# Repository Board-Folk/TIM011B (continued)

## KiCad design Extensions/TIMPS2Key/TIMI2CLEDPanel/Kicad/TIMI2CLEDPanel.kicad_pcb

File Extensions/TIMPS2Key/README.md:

# TIMPS2Key

ATMega/Arduino based PS/2 Keyboard Adapter. Will soon be adding the daughter board for v1.2 or later main boards which will allow fitting within the original board footprint instead of the related serial circuitry and DIN socket.

## Versions

v0 Prototype / Development board using Arduino Nano and a MAX232.

v1 Final Arduino Nano Version. Now includes sound and i2c output for LED panel.

v2 ATMEGA328 Version of v1

## Notes

For use on v1.2 or later main boards with 5V power output selected, bypass voltage regulator at U3 connecting pins 1 and 3

## TIMI2CLEDPanel

This folder contains an I2C connected board to output the keyboard LED display. It's intended to fit within a 3.5" drive blanking front panel blanking plate.

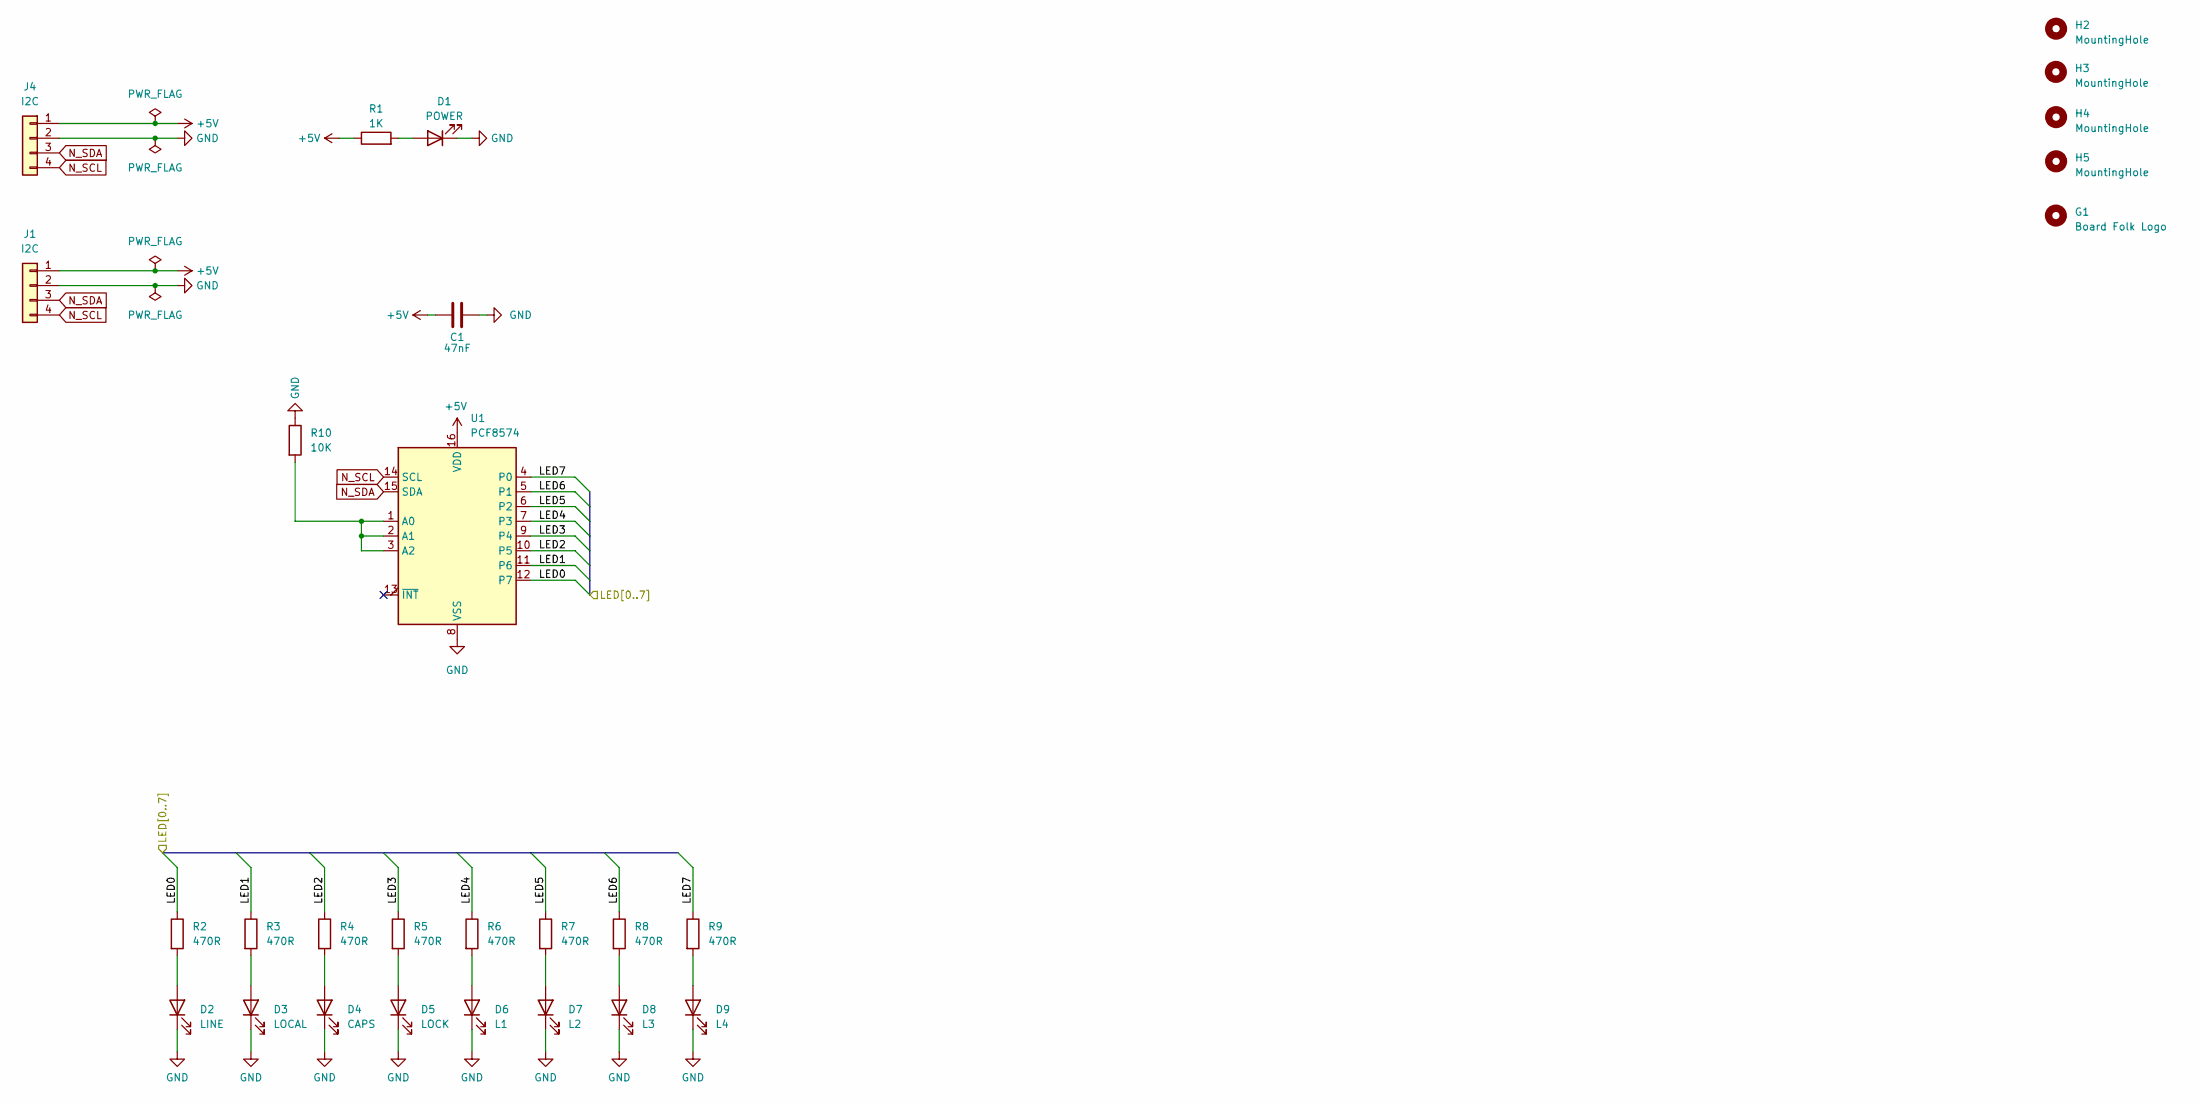
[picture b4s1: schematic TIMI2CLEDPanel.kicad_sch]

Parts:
C1: 47nF; C_Disc_D4.3mm_W1.9mm_P5.00mm
D1: POWER; LED_D3.0mm
D2: LINE; LED_D3.0mm
D3: LOCAL; LED_D3.0mm
D4: CAPS; LED_D3.0mm
D5: LOCK; LED_D3.0mm
D6: L1; LED_D3.0mm
D7: L2; LED_D3.0mm
D8: L3; LED_D3.0mm
D9: L4; LED_D3.0mm
G1: Board Folk Logo; BF8
H2, H3, H4, H5: MountingHole; MountingHole_2.1mm
J1, J4: I2C; PinHeader_1x04_P2.54mm_Vertical
R1: 1K; R_Axial_DIN0204_L3.6mm_D1.6mm_P7.62mm_Horizontal
R2, R3, R4, R5, R6, R7, R8, R9: 470R; R_Axial_DIN0204_L3.6mm_D1.6mm_P7.62mm_Horizontal
R10: 10K; R_Axial_DIN0204_L3.6mm_D1.6mm_P7.62mm_Horizontal
U1: PCF8574; DIP-16_W7.62mm

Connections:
+5V: C1.2, J1.1, J4.1, R1.1, U1.16 (VDD)
/LED0: R2.1, U1.12 (P7)
/LED1: R3.1, U1.11 (P6)
/LED2: R4.1, U1.10 (P5)
/LED3: R5.1, U1.9 (P4)
/LED4: R6.1, U1.7 (P3)
/LED5: R7.1, U1.6 (P2)
/LED6: R8.1, U1.5 (P1)
/LED7: R9.1, U1.4 (P0)
GND: C1.1, D1.1 (K), D2.1 (K), D3.1 (K), D4.1 (K), D5.1 (K), D6.1 (K), D7.1 (K), D8.1 (K), D9.1 (K), J1.2, J4.2, R10.1, U1.8 (VSS)
N_SCL: J1.4, J4.4, U1.14 (SCL)
N_SDA: J1.3, J4.3, U1.15 (SDA)
unnamed: D1.2 (A), R1.2
unnamed: D2.2 (A), R2.2
unnamed: D3.2 (A), R3.2
unnamed: D4.2 (A), R4.2
unnamed: D5.2 (A), R5.2
unnamed: D6.2 (A), R6.2
unnamed: D7.2 (A), R7.2
unnamed: D8.2 (A), R8.2
unnamed: D9.2 (A), R9.2
unnamed: R10.2, U1.1 (A0), U1.2 (A1), U1.3 (A2)

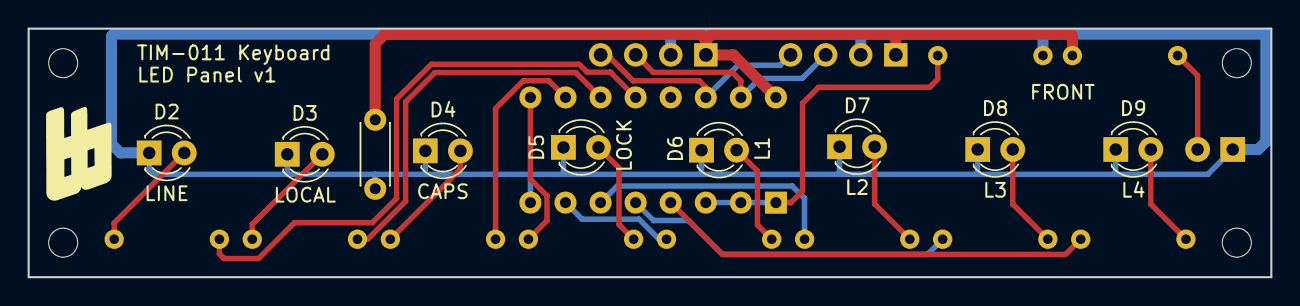
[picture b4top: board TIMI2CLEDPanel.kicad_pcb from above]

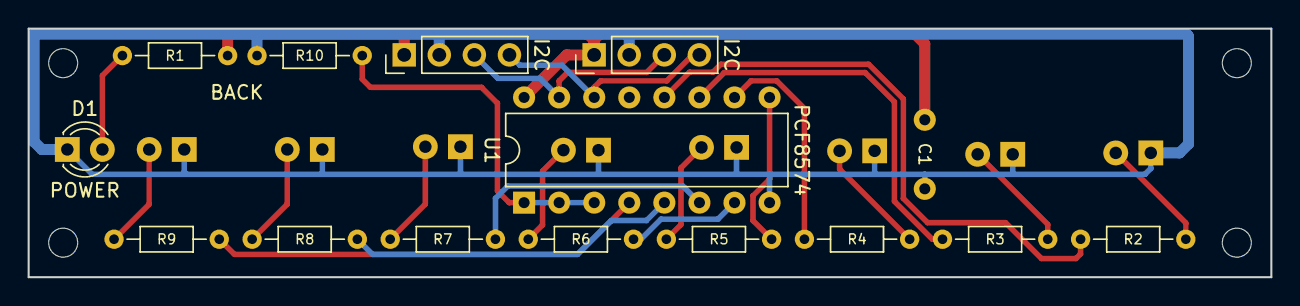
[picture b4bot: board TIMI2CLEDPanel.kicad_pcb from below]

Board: 2 copper layers, 90.0 x 18.0 mm, 28 parts (14 on the bottom side), 22 nets.

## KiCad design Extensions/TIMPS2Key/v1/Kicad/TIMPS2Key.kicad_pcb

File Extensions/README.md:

# TIM-011B Extensions

Extension Boards for the TIM-011B

## TIMPS2Key

ATMega/Arduino based PS/2 Keyboard Adapter.

## TIMAYSound

AY-3-8910/12 expansion board for joystick and sound.

## tim011_video_fix

Video output board to create RGB and composite output from standard TIM-011 video signaling.

## TIMPS2KeyMini

Keyboard daughter card for mainboard v1.2 or later. For fitting a PS/2 keyboard interface within the mainboard footprint.

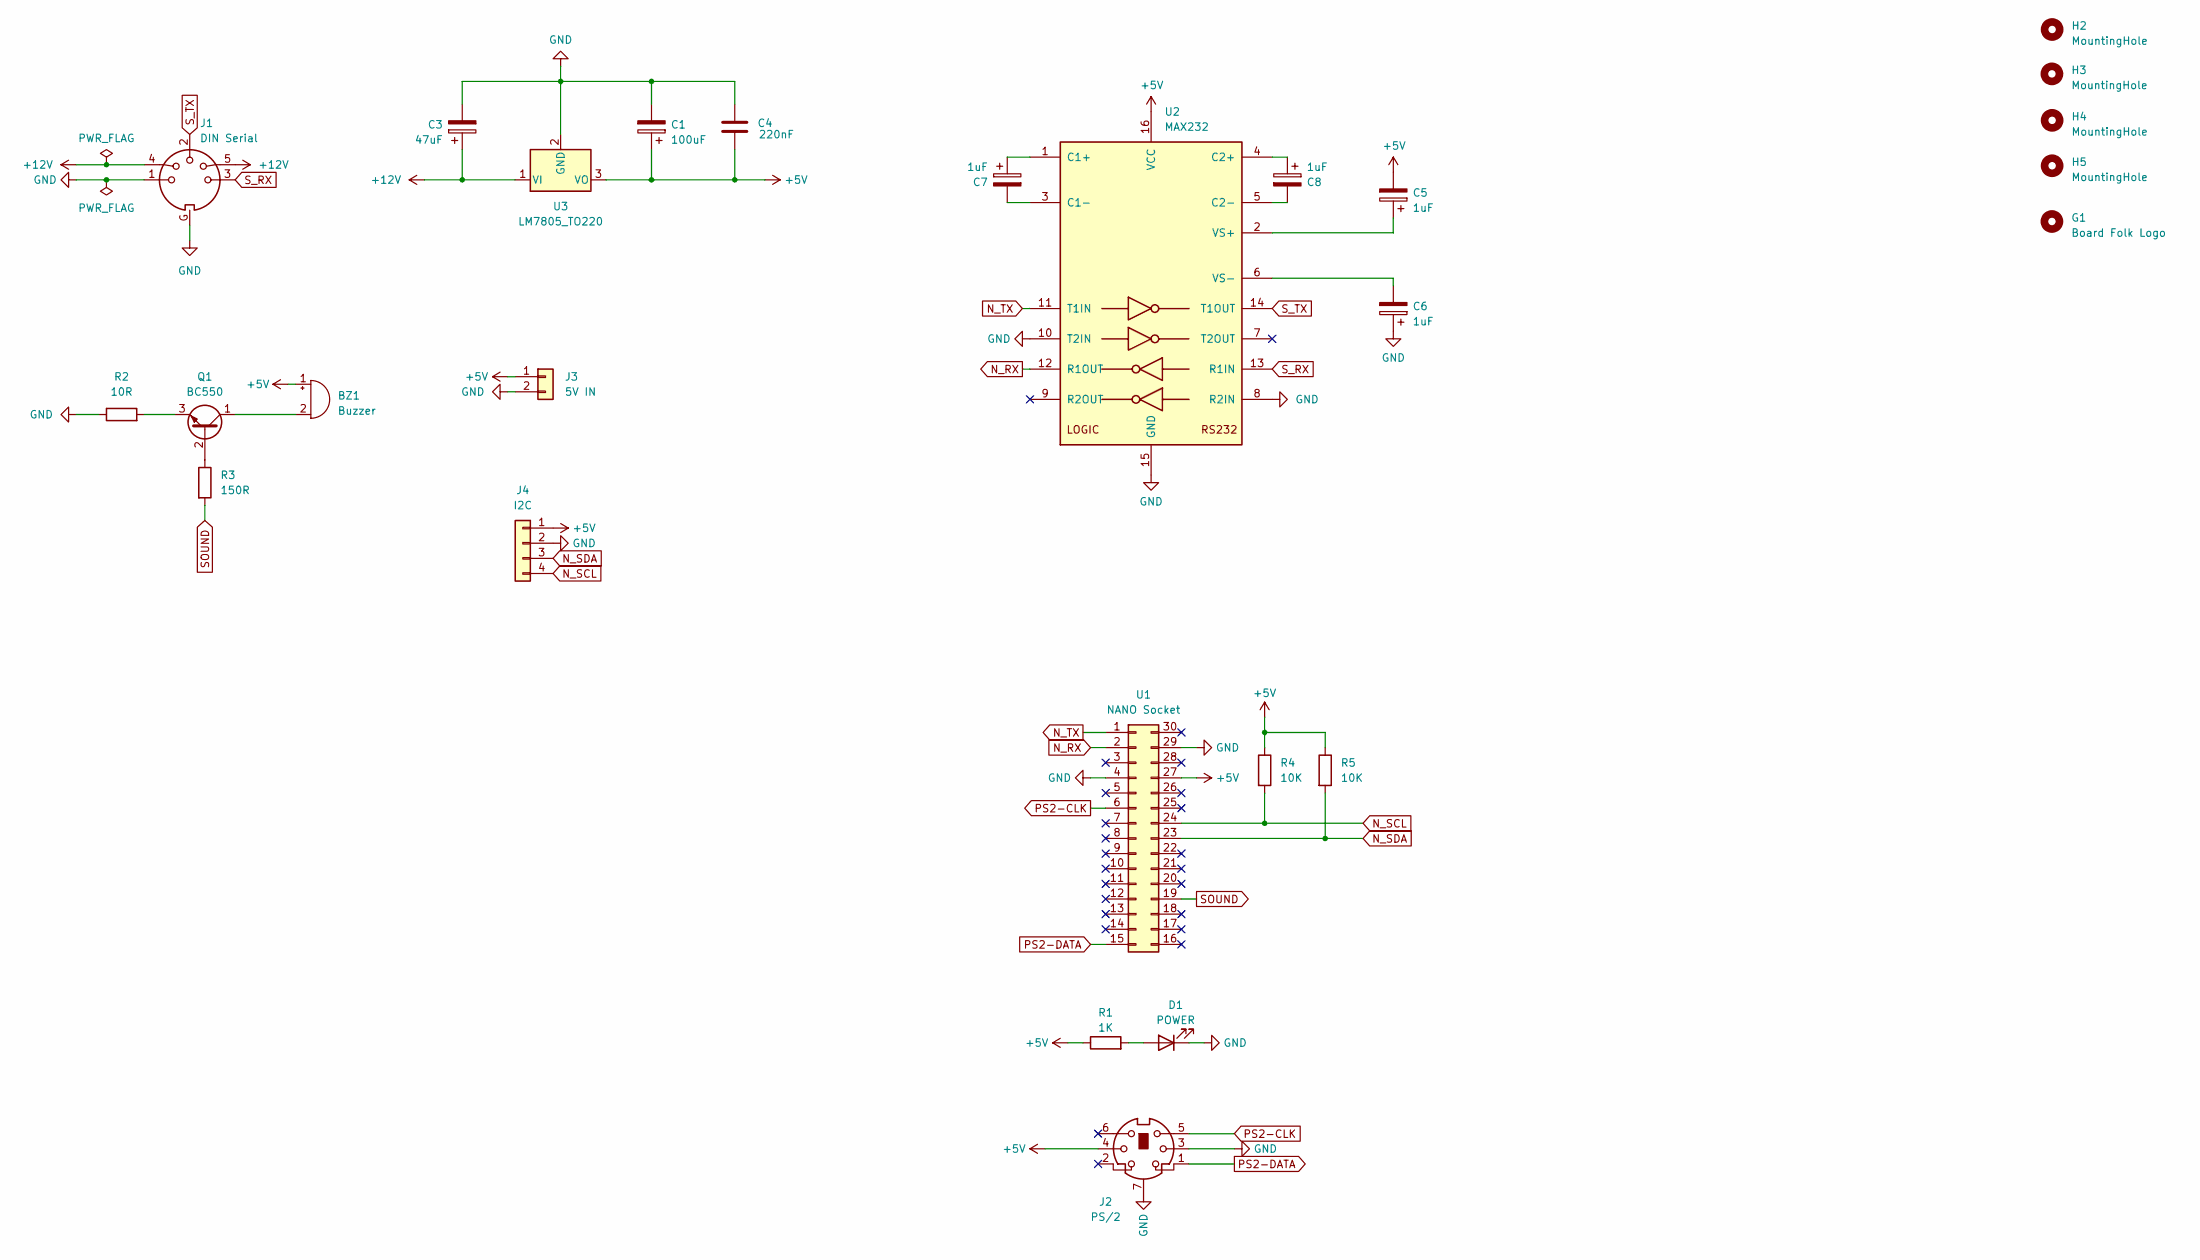
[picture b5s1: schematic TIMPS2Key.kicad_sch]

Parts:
BZ1: Buzzer; MagneticBuzzer_ProSignal_ABT-410-RC
C1: 100uF; CP_Radial_D5.0mm_P2.00mm
C3: 47uF; CP_Radial_D5.0mm_P2.00mm
C4: 220nF; C_Disc_D4.3mm_W1.9mm_P5.00mm
C5, C6, C7, C8: 1uF; CP_Radial_D4.0mm_P2.00mm
D1: POWER; LED_D3.0mm
G1: Board Folk Logo; BF8
H2, H3, H4, H5: MountingHole; MountingHole_2.1mm
J1: DIN Serial; DINSerial
J2: PS/2; Connector_Mini-DIN_Female_6Pin_2rows
J3: 5V IN; PinHeader_1x02_P2.54mm_Vertical
J4: I2C; PinHeader_1x04_P2.54mm_Vertical
Q1: BC550; TO-92_Inline_Wide
R1: 1K; R_Axial_DIN0204_L3.6mm_D1.6mm_P7.62mm_Horizontal
R2: 10R; R_Axial_DIN0204_L3.6mm_D1.6mm_P7.62mm_Horizontal
R3: 150R; R_Axial_DIN0204_L3.6mm_D1.6mm_P7.62mm_Horizontal
R4, R5: 10K; R_Axial_DIN0204_L3.6mm_D1.6mm_P7.62mm_Horizontal
U1: NANO Socket; Arduino_Nano_WithMountingHoles
U2: MAX232; DIP-16_W7.62mm
U3: LM7805_TO220; TO-220-3_Vertical

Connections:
+5V: BZ1.1 (+), C1.1, C4.2, C5.2, J2.4, J3.1, J4.1, R1.1, R4.1, R5.1, U1.27, U2.16 (VCC), U3.3 (VO)
+12V: C3.1, J1.4, J1.5, U3.1 (VI)
GND: C1.2, C3.2, C4.1, C6.1, D1.1 (K), J1.1, J1.G, J2.3, J2.7, J3.2, J4.2, R2.1, U1.4, U1.29, U2.8 (R2IN), U2.10 (T2IN), U2.15 (GND), U3.2 (GND)
N_RX: U1.2, U2.12 (R1OUT)
N_SCL: J4.4, R4.2, U1.24
N_SDA: J4.3, R5.2, U1.23
N_TX: U1.1, U2.11 (T1IN)
unnamed: BZ1.2 (-), Q1.1 (C)
unnamed: D1.2 (A), R1.2
unnamed: Q1.2 (B), R3.1
unnamed: Q1.3 (E), R2.2
unnamed: C7.1, U2.1 (C1+)
unnamed: C7.2, U2.3 (C1-)
unnamed: C8.1, U2.4 (C2+)
unnamed: C8.2, U2.5 (C2-)
unnamed: C5.1, U2.2 (VS+)
unnamed: C6.2, U2.6 (VS-)
PS2-CLK: J2.5, U1.6
PS2-DATA: J2.1, U1.15
SOUND: R3.2, U1.19
S_RX: J1.3, U2.13 (R1IN)
S_TX: J1.2, U2.14 (T1OUT)

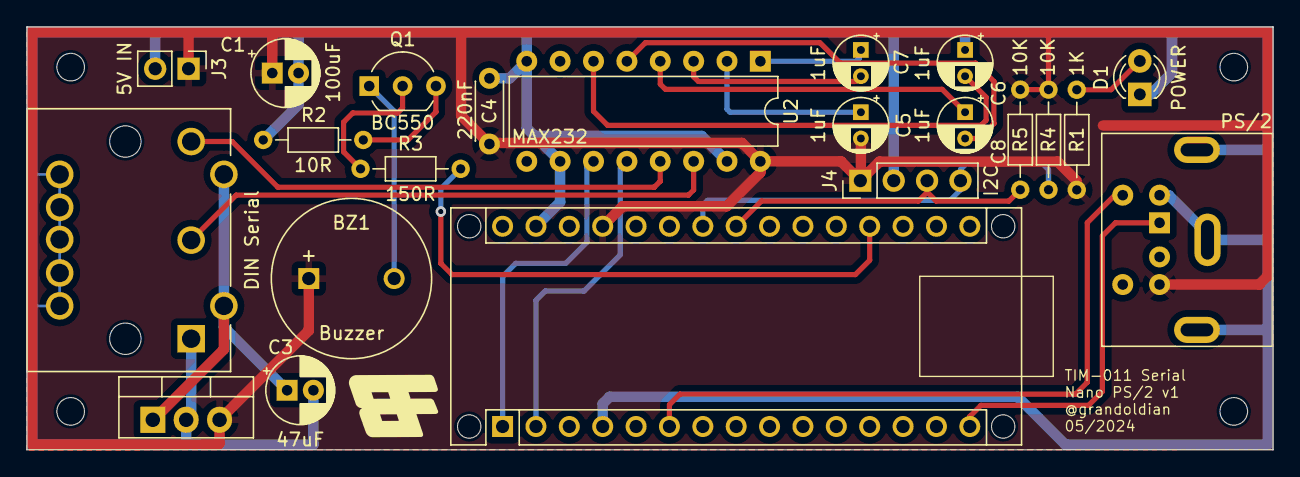
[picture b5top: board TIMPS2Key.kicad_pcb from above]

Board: 2 copper layers, 94.8 x 32.2 mm, 27 parts (0 on the bottom side), 22 nets.

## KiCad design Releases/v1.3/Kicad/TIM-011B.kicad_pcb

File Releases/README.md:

# TIM-011B Releases

Each releases folder contains a Kicad, Gerbers and BOM folder, the latter containing the generated iBOM to help build the board.

Please check out the revision notes, currently on the repository home readme for changes and modifications.

## v1.1

12/04/2024

Initial public release. This doesn't deviate much from the original 1987 board.

## v1.3

16/11/2024

Contains improvements including composite video output, updated oscillators and stability fixes.

## v1.3.1

19/11/2024

Silkscreen fixes only.

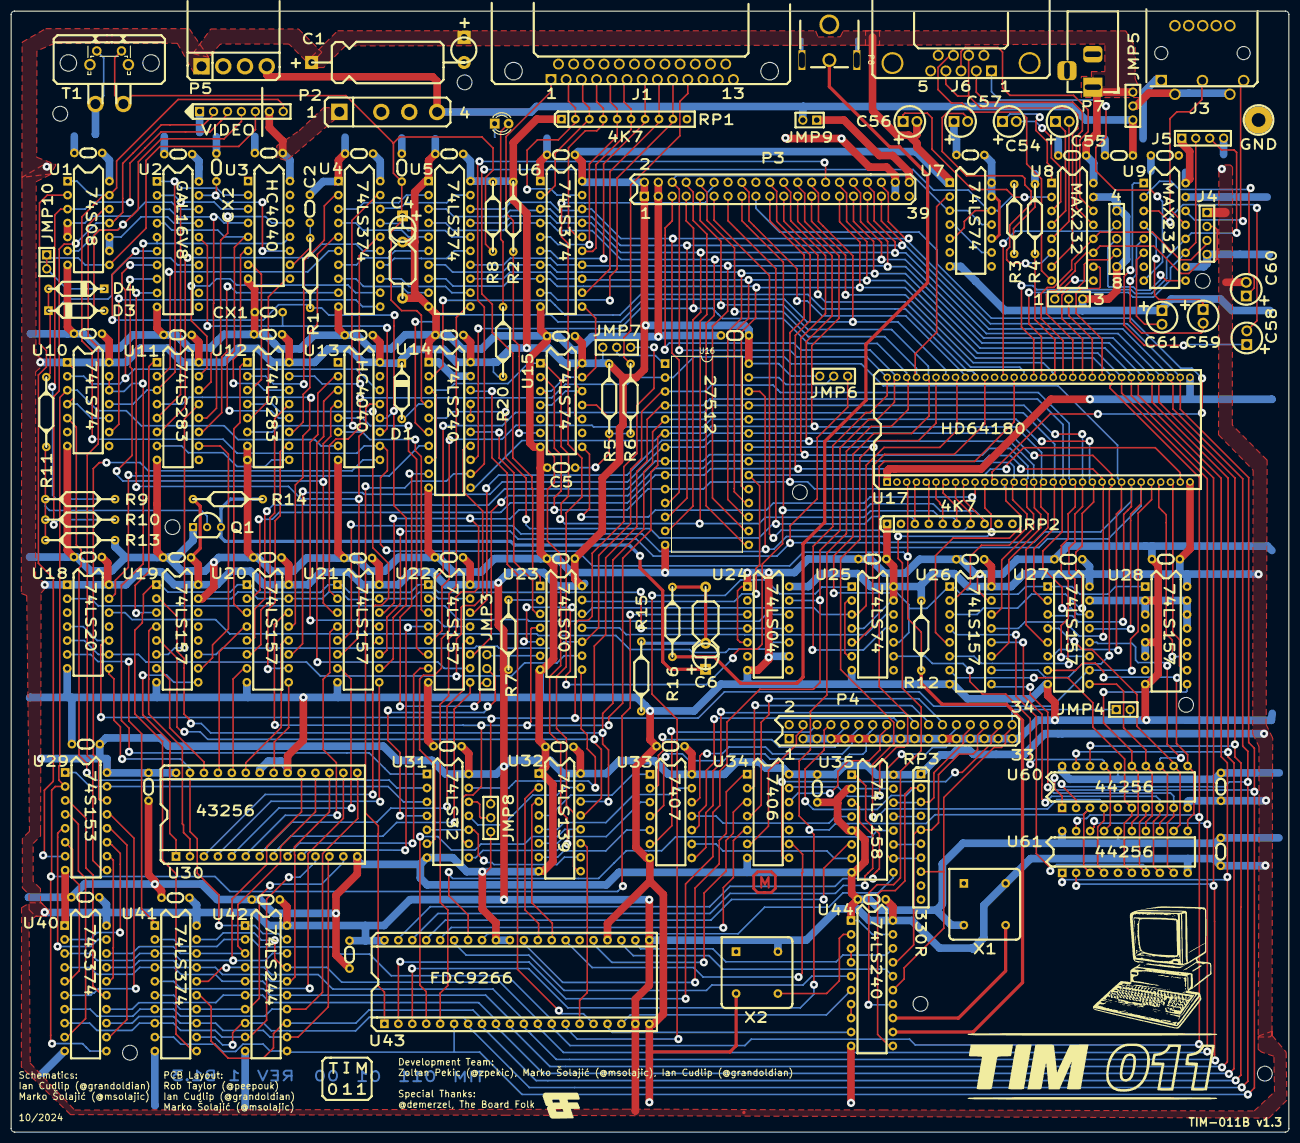
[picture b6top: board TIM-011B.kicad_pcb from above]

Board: 2 copper layers, 232.8 x 204.2 mm, 162 parts (0 on the bottom side), 277 nets.

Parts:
C1: 22uF 25V; Electrolytic Capacitor Axial or Radial
C2: 1nF; Ceramic Cap 5.08mm
C3, C8, C10, C11, C12, C13, C14, C15, C16, C17, C18, C19, C20, C21, C22, C23, C24, C25, C28, C29, C30, C31, C32, C33, C34, C35, C36, C38, C39, C40, C41, C42, C43, C44, C48, C49, C50, C51, C52, C53, C62: 100nF; Ceramic Cap 5.08mm
C4: 10uF; Electrolytic Capacitor Axial or Radial Alt
C5: 2n2; Ceramic Cap 5.08mm
C6: 470uF 25v; Electrolytic Capacitor Axial or Radial Alt
C54, C55, C56, C57, C58, C59, C60, C61: 1uF; Electrolytic Capacitor Radial
CX1, CX2: 330pF; Ceramic Cap 5.08mm
D1, D3, D4: 1N4148; Diode 10.16mm
D2: POWER; LED_D3.0mm
G1: Board Folk Logo; BF8
G2: TIM011 Logo; tim011logo
G3: TIM011 Picture; tim011_picture
H1, H2, H4, H5, H6, H7, H8, H9, H10: MountingHole; MountingHole_M2.5
H3: GND; TIM_MountingHole_2.5mm_Pad
J1: PRINTER
J3: TASTATURA; KEYBOARD2
J4: SERIAL; PinHeader_1x04_2.54mm
J5: KBD; PinHeader_1x04_2.54mm
J6: RS-232/9; SERIAL9
JMP1: Conn_01x03; PinHeader_1x03 2.54mm
JMP2: PinHeader_1x05_2.54mm_Alt
JMP3: XT; PinHeader_1x03 2.54mm
JMP4: FDC Ready; PinHeader_1x02 2.54mm
JMP5: KBPWR; PinHeader_1x03 2.54mm
JMP6: ROMA14; PinHeader_1x03 2.54mm
JMP7: ROMA15; PinHeader_1x03 2.54mm
JMP8: NOVID; PinHeader_1x03 2.54mm
JMP9: 12VEXP; PinHeader_1x02 2.54mm
JMP10: C/HSYNC; PinHeader_1x02 2.54mm
P1: VIDEO; PinHeader_1x07 2.54mm VIDEO
P2: POWER; P2
P3: EXPAND; PinHeader_2x20 2.54mm
P4: DISK; PinHeader_2x17_2.54mm
P5: POWER; 3.96mm Header 4-Pin Edge
P7: 5V Jack; TIM_BarrelJack_Horizontal
P8: Composite; RCA2
Q1: BC557; TO-92_Inline_Wide
R1, R12: 470R; Resistor 12.7mm
R2, R3, R4, R5, R7: 4K7; Resistor 12.7mm
R6: 100R; Resistor 12.7mm
R8: 56K; Resistor 12.7mm
R9: 2K2; Resistor 12.7mm
R10: 1K5; Resistor 12.7mm
R11: 5K1; Resistor 12.7mm
R13, R20: 1K; Resistor 12.7mm
R14: 220R; Resistor 12.7mm
R15: 10K; Resistor 12.7mm
R16: 68R; Resistor 12.7mm
RP1, RP2: 4K7; R_Array_SIP10
RP3: 330R; R_Array_SIP10
T1: RESET; TP1
T2: RESET; SW_Tactile_SPST_Angled_PTS645Vx58-2LFS
U1: 74LS08; DIP-14_W7.62mm
U2: GAL16V8; DIP-20_W7.62mm
U3, U13: 74HC4040; DIP-16_W7.62mm
U4, U5, U6, U40, U41: 74LS374; DIP-20_W7.62mm
U7, U10, U15, U25: 74LS74; DIP-14_W7.62mm
U8, U9: MAX232; DIP-16_W7.62mm
U11, U12: 74LS283; DIP-16_W7.62mm
U14, U44: 74LS240; DIP-20_W7.62mm
U16: 27128; DIP-28_W15.24mm
U17: HD64180; DIP-64_1.78mm Pitch_Socket
U18: 74LS20; DIP-14_W7.62mm
U19, U20, U21, U22, U26, U27, U28: 74LS157; DIP-16_W7.62mm
U23: 74LS00; DIP-14_W7.62mm
U24: 74LS04; DIP-14_W7.62mm
U29: 74HC153; DIP-16_W7.62mm
U30: 43256; DIP-28_W15.24mm_Socket
U31: 74LS32; DIP-14_W7.62mm
U32: 74LS139; DIP-16_W7.62mm
U33: 74LS07; DIP-14_W7.62mm
U34: 74LS06; DIP-14_W7.62mm
U35: 74LS158; DIP-16_W7.62mm
U42: 74LS244; DIP-20_W7.62mm
U43: FDC9266; DIP-40_W15.24mm_Socket
U60, U61: 44256; DIP-20_W7.62mm
X1: 12.288MHz; TIM_Oscillator_DIP-8
X2: 8MHz; TIM_Oscillator_DIP-8

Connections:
+5V: C1.1, C10.1, C11.1, C12.1, C13.1, C14.1, C15.1, C16.1, C17.1, C18.1, C19.1, C20.1, C21.1, C22.1, C23.1, C24.1, C25.1, C28.1, C29.1, C30.1, C31.1, C32.1, C33.1, C34.1, C35.1, C36.1, C38.1, C39.1, C40.1, C41.1, C42.1, C43.1, C44.1, C48.1, C49.1, C50.1, C51.1, C52.1, C53.1, C56.2, C60.2, C62.1, D1.1 (K), J4.1, J5.1, JMP5.3, JMP6.1, JMP7.1, P1.6, P2.1, P3.1, P3.2, P5.1, P7.1, R2.1, R3.2, R4.1, R5.1, R7.1, R8.1, R12.1, R14.1, R20.1, RP1.1 (common), RP2.1 (common), RP3.1 (common), U1.14 (VCC), U2.20 (VCC), U3.16 (VCC), U4.20 (VCC), U5.20 (VCC), U6.20 (VCC), U7.1 (~R), U7.10 (~S), U7.13 (~R), U7.14 (VCC), U8.16 (VCC), U9.16 (VCC), U10.1 (~R), U10.4 (~S), U10.10 (~S), U10.14 (VCC), U11.16 (VCC), U12.16 (VCC), U13.16 (VCC), U14.20 (VCC), U15.4 (~S), U15.10 (~S), U15.12 (D), U15.14 (VCC), U16.28 (VCC), U17.32 (Vcc), U18.1, U18.14 (VCC), U19.16 (VCC), U20.16 (VCC), U21.16 (VCC), U22.16 (VCC), U23.14 (VCC), U24.14 (VCC), U25.4 (~S), U25.13 (~R), U25.14 (VCC), U26.16 (VCC), U27.16 (VCC), U28.16 (VCC), U29.16 (VCC), U30.28 (VCC), U31.14 (VCC), U32.16 (VCC), U33.14 (VCC), U34.14 (VCC), U35.16 (VCC), U40.20 (VCC), U41.20 (VCC), U42.20 (VCC), U43.19 (TEST), U43.21 (MINI), U43.40 (VCC), U44.20 (VCC), U60.10 (VCC), U61.10 (VCC), X1.8 (Vcc), X2.8 (Vcc)
+12V: C8.1, JMP5.1, JMP9.2, P2.4, P5.4
/Addressing/A0: P3.19, U15.2 (D), U16.10 (A0), U17.13 (A0), U21.14 (I0d), U26.5 (I0b), U43.5 (A0)
/Addressing/A1: P3.20, U16.9 (A1), U17.14 (A1), U20.2 (I0a), U26.2 (I0a)
/Addressing/A2: P3.22, U16.8 (A2), U17.15 (A2), U20.5 (I0b), U26.14 (I0d)
/Addressing/A3: P3.23, U16.7 (A3), U17.16 (A3), U20.11 (I0c), U26.11 (I0c)
/Addressing/A4: P3.24, U14.11, U16.6 (A4), U17.17 (A4), U20.14 (I0d), U23.4, U27.5 (I0b), U31.9
/Addressing/A5: U16.5 (A5), U17.18 (A5), U19.2 (I0a), U27.2 (I0a), U32.14 (A0)
/Addressing/A6: U16.4 (A6), U17.19 (A6), U19.5 (I0b), U27.14 (I0d), U32.13 (A1)
/Addressing/A7: U16.3 (A7), U17.20 (A7), U19.11 (I0c), U23.10, U27.11 (I0c)
/Addressing/A8: U16.25 (A8), U17.21 (A8), U22.2 (I0a), U26.6 (I1b)
/Addressing/A9: U16.24 (A9), U17.22 (A9), U22.5 (I0b), U26.3 (I1a)
/Addressing/A10: U16.21 (A10), U17.23 (A10), U22.11 (I0c), U26.13 (I1d)
/Addressing/A11: U16.23 (A11), U17.24 (A11), U22.14 (I0d), U26.10 (I1c)
/Addressing/A12: U16.2 (A12), U17.25 (A12), U21.2 (I0a), U27.6 (I1b)
/Addressing/A13: U16.26 (A13), U17.26 (A13), U21.5 (I0b), U27.3 (I1a)
/Addressing/A14: JMP6.3, U17.27 (A14), U21.11 (I0c), U27.13 (I1d)
/Addressing/A15: JMP7.3, JMP8.1, U17.28 (A15), U18.4, U18.10, U27.10 (I1c)
/Addressing/A16: U17.29 (A16), U28.11 (I0c)
/Addressing/A17: U17.30 (A17), U28.10 (I1c)
/Addressing/A18: U16.20 (~CE), U17.31 (A18/TOUT), U23.13
/CPU/D0: P3.36, U5.18 (D7), U6.18 (D7), U16.11 (D0), U17.34 (D0), U41.9 (O3), U42.11 (I0b), U43.6 (DB0), U60.1 (DQ1)
/CPU/D1: P3.35, U5.3 (D0), U6.3 (D0), U16.12 (D1), U17.35 (D1), U41.12 (O4), U42.8 (I3a), U43.7 (DB1), U60.2 (DQ2)
/CPU/D2: P3.34, U5.17 (D6), U6.17 (D6), U16.13 (D2), U17.36 (D2), U41.15 (O5), U42.13 (I1b), U43.8 (DB2), U60.18 (DQ3)
/CPU/D3: P3.32, U5.4 (D1), U6.4 (D1), U16.15 (D3), U17.37 (D3), U41.6 (O2), U42.6 (I2a), U43.9 (DB3), U60.19 (DQ4)
/CPU/D4: P3.33, U5.14 (D5), U6.14 (D5), U16.16 (D4), U17.38 (D4), U41.5 (O1), U42.15 (I2b), U43.10 (DB4), U61.1 (DQ1)
/CPU/D5: P3.31, U5.7 (D2), U6.7 (D2), U16.17 (D5), U17.39 (D5), U41.16 (O6), U42.4 (I1a), U43.11 (DB5), U61.2 (DQ2)
/CPU/D6: P3.30, U5.13 (D4), U6.13 (D4), U16.18 (D6), U17.40 (D6), U41.19 (O7), U42.17 (I3b), U43.12 (DB6), U61.18 (DQ3)
/CPU/D7: P3.29, U5.8 (D3), U6.8 (D3), U16.19 (D7), U17.41 (D7), U41.2 (O0), U42.2 (I0a), U43.13 (DB7), U61.19 (DQ4)
/RAM/MA0: U26.7 (Zb), U60.6 (A0), U61.6 (A0)
/RAM/MA1: U26.4 (Za), U60.7 (A1), U61.7 (A1)
/RAM/MA2: U26.12 (Zd), U60.8 (A2), U61.8 (A2)
/RAM/MA3: U26.9 (Zc), U60.9 (A3), U61.9 (A3)
/RAM/MA4: U27.7 (Zb), U60.11 (A4), U61.11 (A4)
/RAM/MA5: U27.4 (Za), U60.12 (A5), U61.12 (A5)
/RAM/MA6: U27.12 (Zd), U60.13 (A6), U61.13 (A6)
/RAM/MA7: U27.9 (Zc), U60.14 (A7), U61.14 (A7)
/RAM/MA8: U28.9 (Zc), U60.15 (A8), U61.15 (A8)
/Video/IO0: U30.11 (Q0), U40.8 (D3), U41.8 (D3), U42.9 (O0b)
/Video/IO1: U30.12 (Q1), U40.13 (D4), U41.13 (D4), U42.12 (O3a)
/Video/IO2: U30.13 (Q2), U40.14 (D5), U41.14 (D5), U42.7 (O1b)
/Video/IO3: U30.15 (Q3), U40.7 (D2), U41.7 (D2), U42.14 (O2a)
/Video/IO4: U30.16 (Q4), U40.4 (D1), U41.4 (D1), U42.5 (O2b)
/Video/IO5: U30.17 (Q5), U40.17 (D6), U41.17 (D6), U42.16 (O1a)
/Video/IO6: U30.18 (Q6), U40.18 (D7), U41.18 (D7), U42.3 (O3b)
/Video/IO7: U30.19 (Q7), U40.3 (D0), U41.3 (D0), U42.18 (O0a)
/Video/OFFSETC: C6.1, Q1.3 (E), R14.2
/Video/VA0: U22.4 (Za), U30.10 (A0)
/Video/VA1: U22.7 (Zb), U30.9 (A1)
/Video/VA2: U22.9 (Zc), U30.8 (A2)
/Video/VA3: U22.12 (Zd), U30.7 (A3)
/Video/VA4: U21.4 (Za), U30.6 (A4)
/Video/VA5: U21.7 (Zb), U30.5 (A5)
/Video/VA6: U21.9 (Zc), U30.4 (A6)
/Video/VA7: U21.12 (Zd), U30.3 (A7)
/Video/VA8: U20.4 (Za), U30.25 (A8)
/Video/VA9: U20.7 (Zb), U30.24 (A9)
/Video/VA10: U20.9 (Zc), U30.21 (A10)
/Video/VA11: U20.12 (Zd), U30.23 (A11)
/Video/VA12: U19.4 (Za), U30.2 (A12)
/Video/VA13: U19.7 (Zb), U30.26 (A13)
/Video/VA14: U19.9 (Zc), U30.1 (A14)
CLK: P1.7, R12.2, U1.1, U1.13, U13.10 (~CP), U17.3 (EXTAL), U44.12
CLK8: U43.22 (CLK), U44.18
E: P3.9, U17.60 (E), U25.10 (~S), U26.1 (S), U27.1 (S), U28.1 (S)
EXPSEL_O: P3.12, U32.9 (O3)
FDCDMA_0: U32.11 (O1), U43.15 (~DACK)
FDCSEL_0: U32.12 (O0), U43.4 (~CS)
FI: P3.6, U7.3 (C), U7.11 (C), U17.64 (Ø), U25.11 (C)
GND: C1.2, C2.2, C3.2, C4.2, C5.2, C8.2, C10.2, C11.2, C12.2, C13.2, C14.2, C15.2, C16.2, C17.2, C18.2, C19.2, C20.2, C21.2, C22.2, C23.2, C24.2, C25.2, C28.2, C29.2, C30.2, C31.2, C32.2, C33.2, C34.2, C35.2, C36.2, C38.2, C39.2, C40.2, C41.2, C42.2, C43.2, C44.2, C48.2, C49.2, C50.2, C51.2, C52.2, C53.2, C57.1, C61.1, C62.2, CX1.2, CX2.2, D2.1 (K), H3.1, J1.18, J1.19, J1.20, J1.21, J1.22, J1.23, J1.24, J1.25, J3.1, J4.4, J5.4, J6.0 (PAD), J6.5, JMP1.3, JMP2.1, JMP2.5, JMP4.2, JMP8.3, P1.1, P2.2, P3.3, P3.4, P3.37, P3.38, P4.3, P4.5, P4.7, P4.9, P4.11, P4.13, P4.15, P4.17, P4.19, P4.21, P4.23, P4.25, P4.27, P4.29, P4.31, P4.33, P5.2, P7.2, P7.3, P8.2 (Ext), Q1.1 (C), R13.2, R15.2, T1.1, T2.1, U1.7 (GND), U2.10 (GND), U3.8 (GND), U4.1 (OE), U4.10 (GND), U5.1 (OE), U5.10 (GND), U6.1 (OE), U6.10 (GND), U7.7 (GND), U8.15 (GND), U9.10 (T2IN), U9.15 (GND), U10.7 (GND), U11.8 (GND), U12.7 (C0), U12.8 (GND), U13.8 (GND), U14.1, U14.10 (GND), U14.19, U15.7 (GND), U16.14 (GND), U17.1 (Vss), U17.33 (Vss), U18.7 (GND), U19.8 (GND), U19.15 (E), U20.8 (GND), U20.15 (E), U21.8 (GND), U21.15 (E), U22.8 (GND), U22.15 (E), U23.7 (GND), U24.1, U24.5, U24.7 (GND), U24.9, U25.7 (GND), U26.8 (GND), U26.15 (E), U27.8 (GND), U27.15 (E), U28.2 (I0a), U28.3 (I1a), U28.5 (I0b), U28.6 (I1b), U28.8 (GND), U28.13 (I1d), U28.14 (I0d), U28.15 (E), U29.8 (GND), U30.14 (GND), U30.20 (~CS), U30.22 (~OE), U31.7 (GND), U32.1 (E), U32.8 (GND), U33.7 (GND), U34.7 (GND), U35.2 (I0a), U35.5 (I0b), U35.8 (GND), U35.15 (E), U40.1 (OE), U40.10 (GND), U41.10 (GND), U42.10 (GND), U43.20 (VSS), U43.24 (P0), U43.31 (P1), U43.32 (P2), U44.1, U44.10 (GND), U44.19, U60.16 (~OE), U60.20 (VSS), U61.16 (~OE), U61.20 (VSS), X1.4 (GND), X2.4 (GND)
HQ6: U2.8 (I8), U13.4 (Q6), U21.3 (I1a)
HQ7: U2.9 (I9), U13.13 (Q7), U21.6 (I1b)
HQ8: R1.1, U2.6 (I6), U13.12 (Q8), U21.10 (I1c)
HQ9: U2.7 (I7), U10.2 (D), U13.14 (Q9)
HRESET: CX1.1, U2.16 (IO4), U13.11 (MR)
IOE: U14.14, U18.5, U18.9, U23.9
J_CTS: J6.8, U8.8 (R2IN)
J_DCD: J6.1, U9.8 (R2IN)
J_RTS: J6.4, J6.7, U8.7 (T2OUT)
J_RX: J6.2, U8.13 (R1IN)
J_TX: J6.3, U8.14 (T1OUT)
K_RX: J3.2, U9.13 (R1IN)
K_TX: J3.3, U9.14 (T1OUT)
unnamed: C6.2, R15.1, R16.1
unnamed: C3.1, C4.1, D1.2 (A), R8.2, T1.2, T2.2, U14.4
unnamed: D2.2 (A), R20.2
unnamed: J1.10, R6.2
unnamed: J3.4, J3.5, JMP5.2
unnamed: JMP3.1, U14.9
unnamed: JMP3.2, U31.4
unnamed: JMP3.3, U23.6
unnamed: JMP6.2, U16.27 (A14)
unnamed: JMP7.2, U16.1 (A15)
unnamed: JMP8.2, U31.12
unnamed: JMP9.1, P3.40
unnamed: P8.1 (In), R16.2
unnamed: Q1.2 (B), R9.1, R10.1, R11.1, R13.1
unnamed: R7.2, U23.2
unnamed: J1.2, RP1.2 (R1), U6.19 (O7)
unnamed: J1.3, RP1.3 (R2), U6.2 (O0)
unnamed: J1.4, RP1.4 (R3), U6.16 (O6)
unnamed: J1.5, RP1.5 (R4), U6.5 (O1)
unnamed: J1.6, RP1.6 (R5), U6.15 (O5)
unnamed: J1.7, RP1.7 (R6), U6.6 (O2)
unnamed: J1.8, RP1.8 (R7), U6.12 (O4)
unnamed: J1.9, RP1.9 (R8), U6.9 (O3)
unnamed: RP3.4 (R3), U35.13 (I1c)
unnamed: RP3.6 (R5), U35.11 (I0d)
unnamed: U1.9, U1.10, U2.17 (I03)
unnamed: U1.4, U1.5, U2.18 (IO2)
unnamed: C2.1, R1.2, U3.10 (~CP)
unnamed: U4.3 (D0), U5.2 (O0)
unnamed: U4.4 (D1), U5.5 (O1)
unnamed: U4.7 (D2), U5.6 (O2)
unnamed: U4.8 (D3), U5.9 (O3)
unnamed: U4.13 (D4), U5.12 (O4)
unnamed: U4.14 (D5), U5.15 (O5)
unnamed: U4.17 (D6), U5.16 (O6)
unnamed: U4.18 (D7), U5.19 (O7)
unnamed: R3.1, U7.5 (Q), U7.12 (D), U23.1
unnamed: U7.4 (~S), U7.9 (Q)
unnamed: C54.1, U8.1 (C1+)
unnamed: C54.2, U8.3 (C1-)
unnamed: C55.1, U8.4 (C2+)
unnamed: C55.2, U8.5 (C2-)
unnamed: C56.1, U8.2 (VS+)
unnamed: C57.2, U8.6 (VS-)
unnamed: C58.1, U9.1 (C1+)
unnamed: C58.2, U9.3 (C1-)
unnamed: C59.1, U9.4 (C2+)
unnamed: C59.2, U9.5 (C2-)
unnamed: C60.1, U9.2 (VS+)
unnamed: C61.2, U9.6 (VS-)
unnamed: U10.5 (Q), U31.2
unnamed: U4.11 (Cp), U10.9 (Q)
unnamed: U3.13 (Q7), U11.12 (A4)
unnamed: U4.15 (O5), U11.6 (B1)
unnamed: U4.6 (O2), U11.2 (B2)
unnamed: U4.12 (O4), U11.15 (B3)
unnamed: U4.9 (O3), U11.11 (B4)
unnamed: U11.7 (C0), U12.9 (C4)
unnamed: U11.4 (S1), U20.13 (I1d)
unnamed: U11.1 (S2), U19.3 (I1a)
unnamed: U11.13 (S3), U19.6 (I1b)
unnamed: U11.10 (S4), U19.10 (I1c)
unnamed: U3.9 (Q0), U12.5 (A1)
unnamed: U3.7 (Q1), U12.3 (A2)
unnamed: U3.6 (Q2), U12.14 (A3)
unnamed: U4.19 (O7), U12.6 (B1)
unnamed: U4.2 (O0), U12.2 (B2)
unnamed: U4.16 (O6), U12.15 (B3)
unnamed: U4.5 (O1), U12.11 (B4)
unnamed: U12.4 (S1), U21.13 (I1d)
unnamed: U12.1 (S2), U20.3 (I1a)
unnamed: U12.13 (S3), U20.6 (I1b)
unnamed: U12.10 (S4), U20.10 (I1c)
unnamed: U13.6 (Q2), U22.3 (I1a)
unnamed: U13.5 (Q3), U22.6 (I1b)
unnamed: U13.3 (Q4), U22.10 (I1c)
unnamed: U13.2 (Q5), U22.13 (I1d)
unnamed: U14.7, U18.13
unnamed: U14.15, U23.3
unnamed: U14.16, U14.17
unnamed: J1.1, R2.2, U15.6 (~Q)
unnamed: C5.1, R5.2, R6.1, U15.11 (C)
unnamed: U18.2, U24.12
unnamed: U18.12, U24.10
unnamed: U23.8, U31.13
unnamed: U25.2 (D), U25.6 (~Q)
unnamed: U25.1 (~R), U43.14 (DRQ)
unnamed: U23.11, U25.12 (D)
unnamed: U29.1 (Ea), U29.15 (Eb), U31.3
unnamed: U29.6 (I0a), U40.5 (O1)
unnamed: U29.10 (I0b), U40.16 (O6)
unnamed: U29.5 (I1a), U40.19 (O7)
unnamed: U29.11 (I1b), U40.2 (O0)
unnamed: U29.4 (I2a), U40.9 (O3)
unnamed: U29.12 (I2b), U40.12 (O4)
unnamed: U29.3 (I3a), U40.15 (O5)
unnamed: U29.13 (I3b), U40.6 (O2)
unnamed: U1.2, U29.7 (Za)
unnamed: U1.12, U29.9 (Zb)
unnamed: U32.2 (A0), U43.29 (DS0)
unnamed: U32.3 (A1), U43.28 (DS1)
unnamed: U32.4 (O0), U33.1
unnamed: U32.5 (O1), U33.13
unnamed: U32.6 (O2), U33.3
unnamed: U32.7 (O3), U33.5
unnamed: U31.11, U32.15 (E)
unnamed: U31.5, U31.10, U32.10 (O2)
unnamed: U35.3 (I1a), U43.38 (LCT_DIR)
unnamed: U35.6 (I1b), U43.37 (STEP)
unnamed: U35.1 (S), U43.39 (~RW_SEEK)
unnamed: U33.11, U35.4 (Za)
unnamed: U33.9, U35.7 (Zb)
unnamed: U35.12 (Zc), U43.34 (WP/TS)
unnamed: U35.9 (Zd), U43.33 (FLT/TR0)
unnamed: U18.6, U41.1 (OE)
unnamed: U34.5, U43.36 (HDL)
unnamed: U43.17 (IDX), U44.9
unnamed: U43.18 (INT), U44.6
unnamed: U43.35 (RDY), U44.5
unnamed: U34.9, U43.27 (SIDE)
unnamed: U14.18, U43.16 (TC)
unnamed: U34.1, U43.30 (WDOUT)
unnamed: U34.3, U43.25 (WE)
unnamed: U43.23 (~DSKD), U44.16
unnamed: U44.3, U44.4
unnamed: U44.7, U44.8
unnamed: U44.13, X1.5 (OUT)
unnamed: U44.2, X2.5 (OUT)
PRINT_O: U6.11 (Cp), U15.3 (C), U15.13 (~R), U31.8
RESET: P3.28, U14.12, U43.1 (RST)
RX0: J4.3, U8.12 (R1OUT), U17.46 (RXA0)
RX1: J5.3, U9.12 (R1OUT), U17.49 (RXA1)
SCROLL_O: U5.11 (Cp), U31.6
ST: P3.17, U17.12 (ST)
TX0: J4.2, U8.11 (T1IN), U17.45 (TXA0)
TX1: J5.2, U9.11 (T1IN), U17.48 (TXA1)
TXS: U17.51 (TXS), U34.13
VID1: P1.2, R10.2, U1.11
VID2: P1.3, R9.2, U1.3
VIDCLK: U10.3 (C), U13.7 (Q1), U24.3, U29.2 (S1), U40.11 (Cp)
VIDCLK2: U13.9 (Q0), U29.14 (S0)
VQ3: U2.4 (I4), U3.5 (Q3), U12.12 (A4)
VQ4: U2.2 (I2), U3.3 (Q4), U11.5 (A1)
VQ5: U2.1 (I1/CLK), U3.2 (Q5), U10.11 (C), U11.3 (A2)
VQ6: U2.3 (I3), U3.4 (Q6), U11.14 (A3)
VQ8: U2.5 (I5), U3.12 (Q8), U10.12 (D), U10.13 (~R), U31.1
VRESET: CX2.1, U2.19 (IO1), U3.11 (MR)
X_CTS: JMP1.1, U8.9 (R2OUT)
X_DCD: JMP2.3, U9.9 (R2OUT)
fDIR: P4.18, U33.10
fDRIVE0: P4.10, U33.2
fDRIVE1: P4.12, U33.12
fDRIVE2: P4.14, U33.4
fDRIVE3: P4.6, U33.6
fINDEX: P4.8, RP3.2 (R1), U44.11
fINUSE: P4.4, U34.6
fMOTOR1: P4.16, U34.12
fREAD: P4.30, RP3.5 (R4), U44.17
fREADY: JMP4.1, P4.34, RP3.8 (R7), U44.15
fSIDE1: P4.32, U34.8
fSTEP: P4.20, U33.8
fTRACK0: P4.26, RP3.7 (R6), U35.10 (I1d)
fWDATA: P4.22, U34.2
fWGATE: P4.24, U34.4
fWRITEPROT: P4.28, RP3.3 (R2), U35.14 (I0c)
~BUSACK: RP2.4 (R3), U17.5 (~BUSACK)
~BUSREQ: RP2.5 (R4), U17.6 (~BUSREQ)
~CAS: U25.9 (Q), U60.17 (~CAS), U61.17 (~CAS)
~CSYNC: D3.1 (K), D4.2 (A), R11.2, U2.14 (IO6)
~CTS0: JMP1.2, U17.43 (~CTS0)
~CTS1: JMP2.2, U17.52 (RXS/~CTS1)
~DCD0: JMP2.4, U17.44 (~DCD0)
~DREQ0: P3.25, R4.2, U17.47 (CKA0/~DREQ0)
~DREQ1: U17.54 (~DREQ1), U25.5 (Q)
~HALT: P3.16, U17.56 (~HALT)
~HSYNC: D4.1 (K), JMP10.1, JMP10.2, P1.5, U1.8
~INT0: P3.15, RP2.8 (R7), U17.9 (~INT0), U23.5
~INT1: U15.8 (~Q), U17.10 (~INT1)
~INT2: U17.11 (~INT2), U44.14
~IOE: P3.26, U14.6, U17.58 (~IOE)
~LIR: P3.10, U7.2 (D), U17.61 (~LIR)
~ME: U16.22 (~OE), U17.59 (~ME), U60.4 (~RAS), U61.4 (~RAS)
~NMI: P3.11, RP2.7 (R6), U17.8 (~NMI)
~RD: P3.5, U17.63 (~RD), U24.13, U43.2 (~RD)
~REF: U17.57 (~REF), U23.12, U25.3 (C)
~RESET: P3.8, RP2.6 (R5), U14.3, U14.8, U15.1 (~R), U17.7 (~RESET)
~RTS0: U8.10 (T2IN), U17.42 (~RTS0)
~TEND0: P3.21, U17.50 (CKA1/~TEND0)
~TEND1: U14.2, U17.55 (~TEND1)
~VIDCLK: U19.1 (S), U20.1 (S), U21.1 (S), U22.1 (S), U24.4, U24.11, U41.11 (Cp)
~VSYNC: D3.2 (A), P1.4, U1.6
~VWR: U18.8, U30.27 (~WE), U42.1 (OEa), U42.19 (OEb)
~WAIT: P3.13, RP2.3 (R2), U14.5, U17.4 (~WAIT)
~WR: P3.7, U14.13, U17.62 (~WR), U43.3 (~WR), U60.3 (~W), U61.3 (~W)
